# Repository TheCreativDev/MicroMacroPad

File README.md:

# Micro-Macro-Pad!

A small design with 4 Switches and 2 Rotary Encoders for maximum freedom with hotkeys. It's the first hardware I designed, and the first time I worked with both KiCad and Autodesk Fusion, but which was easy and fun to get started thanks to the resources on https://blueprint.hackclub.com/hackpad

## Features
- runs on KMK
- added a little animation that flashes the OLED in a wave pattern on every keystroke

## BOM
- 1 Seeed XIAO RP2040
- 4 MX-Style Switches
- 4 blank DSA keycaps
- 2 EC11 Rotary encoders
- 1 0.91 inch OLED display
- 5 M3x16mm screws
- 5 M3x5mmx4mm heatset inserts
- 6 1N4148 Diodes

## Images of the pad

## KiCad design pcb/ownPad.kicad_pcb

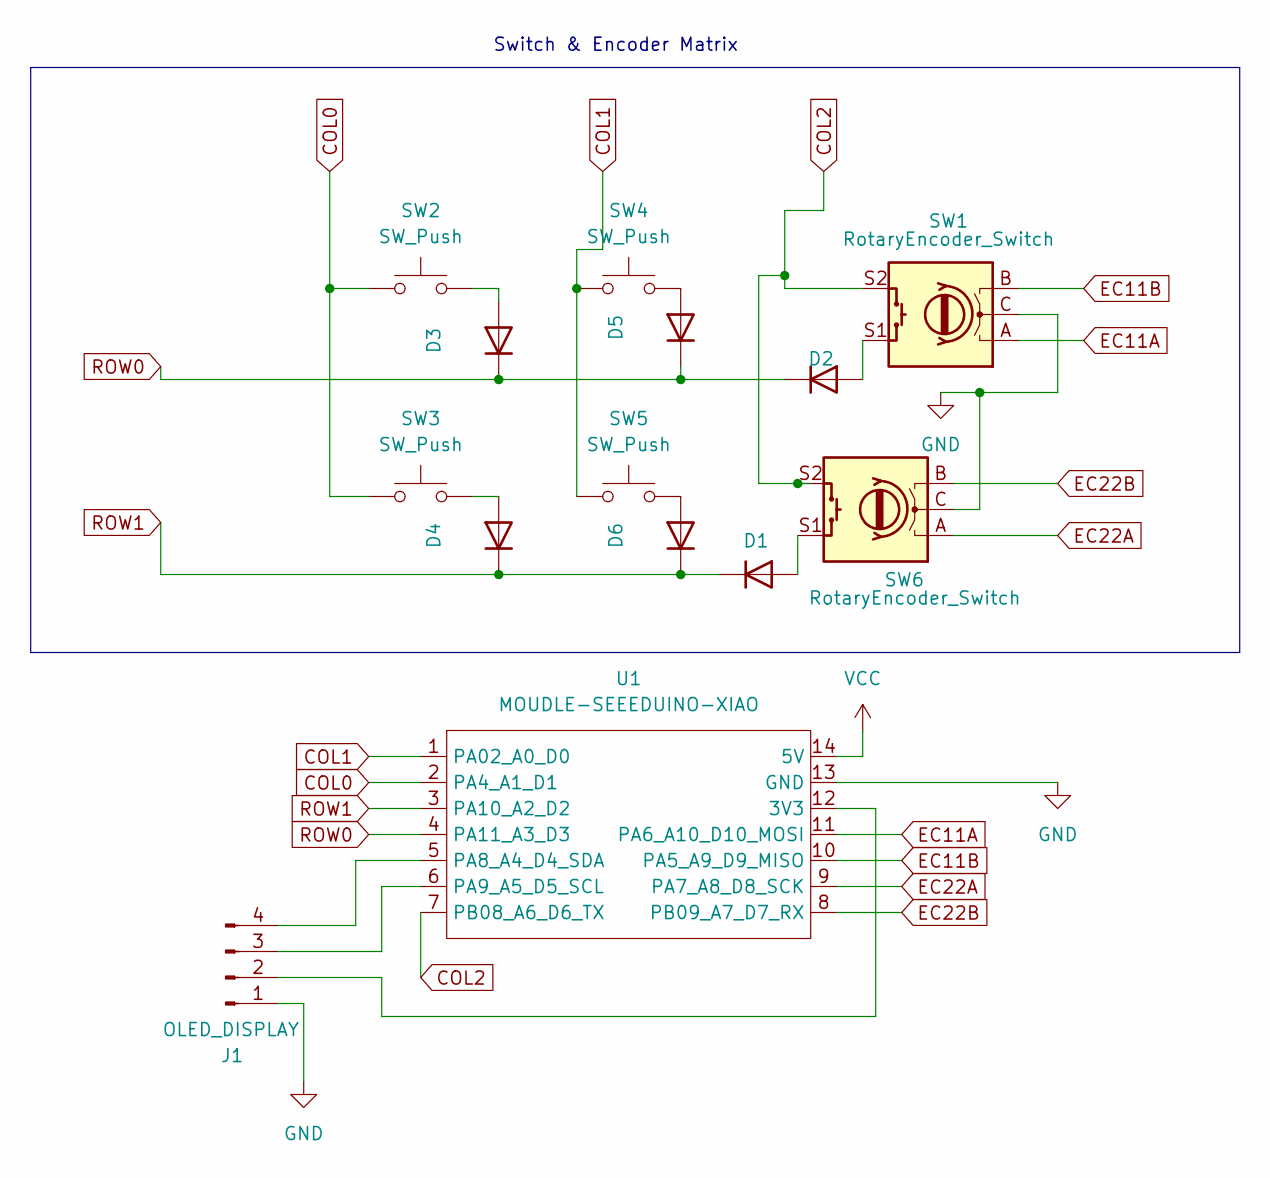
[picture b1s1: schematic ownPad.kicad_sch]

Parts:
D1, D2, D3, D4, D5, D6: D_DO-35_SOD27_P7.62mm_Horizontal
J1: OLED_DISPLAY; SSD1306-0.91-OLED-4pin-128x32
SW1, SW6: RotaryEncoder_Switch; RotaryEncoder_Alps_EC11E-Switch_Vertical_H20mm
SW2, SW3, SW4, SW5: SW_Push; SW_Cherry_MX_1.00u_PCB
U1: MOUDLE-SEEEDUINO-XIAO; XIAO-Generic-Hybrid-14P-2.54-21X17.8MM

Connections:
COL0: SW2.1, SW3.1, U1.2 (PA4_A1_D1)
COL1: SW4.1, SW5.1, U1.1 (PA02_A0_D0)
COL2: SW1.S2, SW6.S2, U1.7 (PB08_A6_D6_TX)
EC11A: SW1.A, U1.11 (PA6_A10_D10_MOSI)
EC11B: SW1.B, U1.10 (PA5_A9_D9_MISO)
EC22A: SW6.A, U1.9 (PA7_A8_D8_SCK)
EC22B: SW6.B, U1.8 (PB09_A7_D7_RX)
GND: J1.1, SW1.C, SW6.C, U1.13 (GND)
unnamed: D1.2 (A), SW6.S1
unnamed: D2.2 (A), SW1.S1
unnamed: D3.2 (A), SW2.2
unnamed: D4.2 (A), SW3.2
unnamed: D5.2 (A), SW4.2
unnamed: D6.2 (A), SW5.2
unnamed: J1.2, U1.12 (3V3)
unnamed: J1.3, U1.6 (PA9_A5_D5_SCL)
unnamed: J1.4, U1.5 (PA8_A4_D4_SDA)
ROW0: D2.1 (K), D3.1 (K), D5.1 (K), U1.4 (PA11_A3_D3)
ROW1: D1.1 (K), D4.1 (K), D6.1 (K), U1.3 (PA10_A2_D2)
VCC: U1.14 (5V)

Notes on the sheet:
Switch & Encoder Matrix

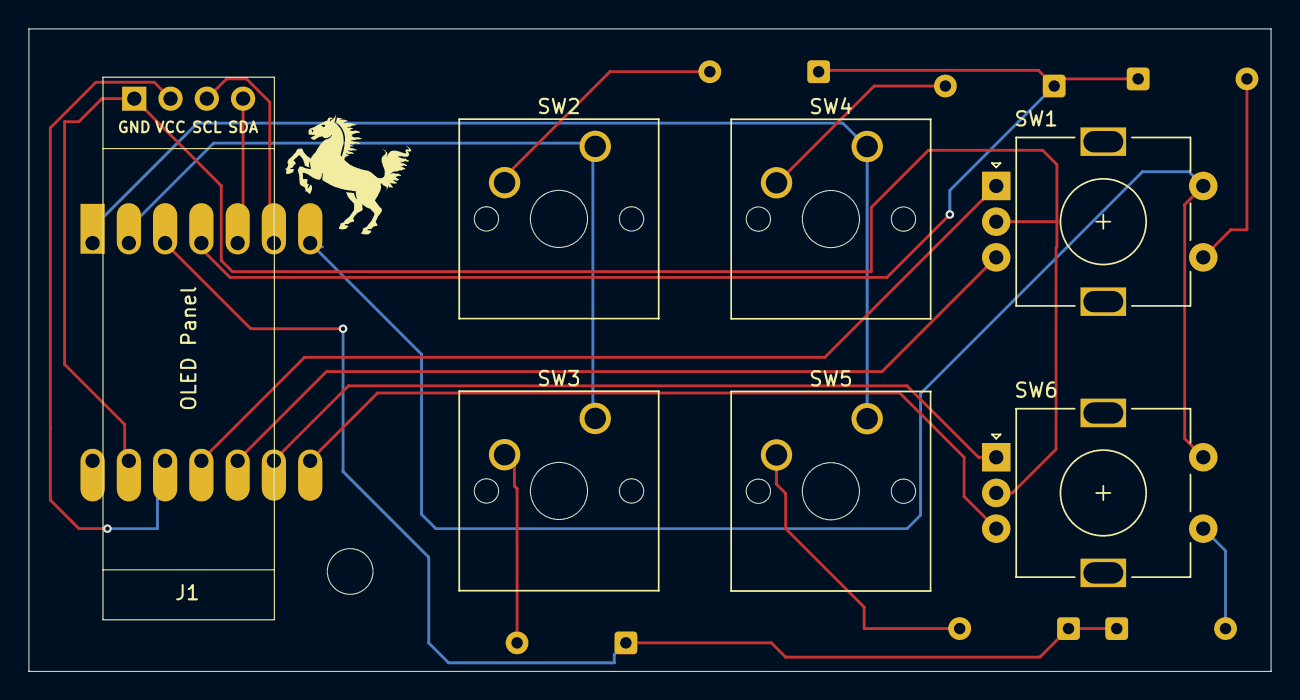
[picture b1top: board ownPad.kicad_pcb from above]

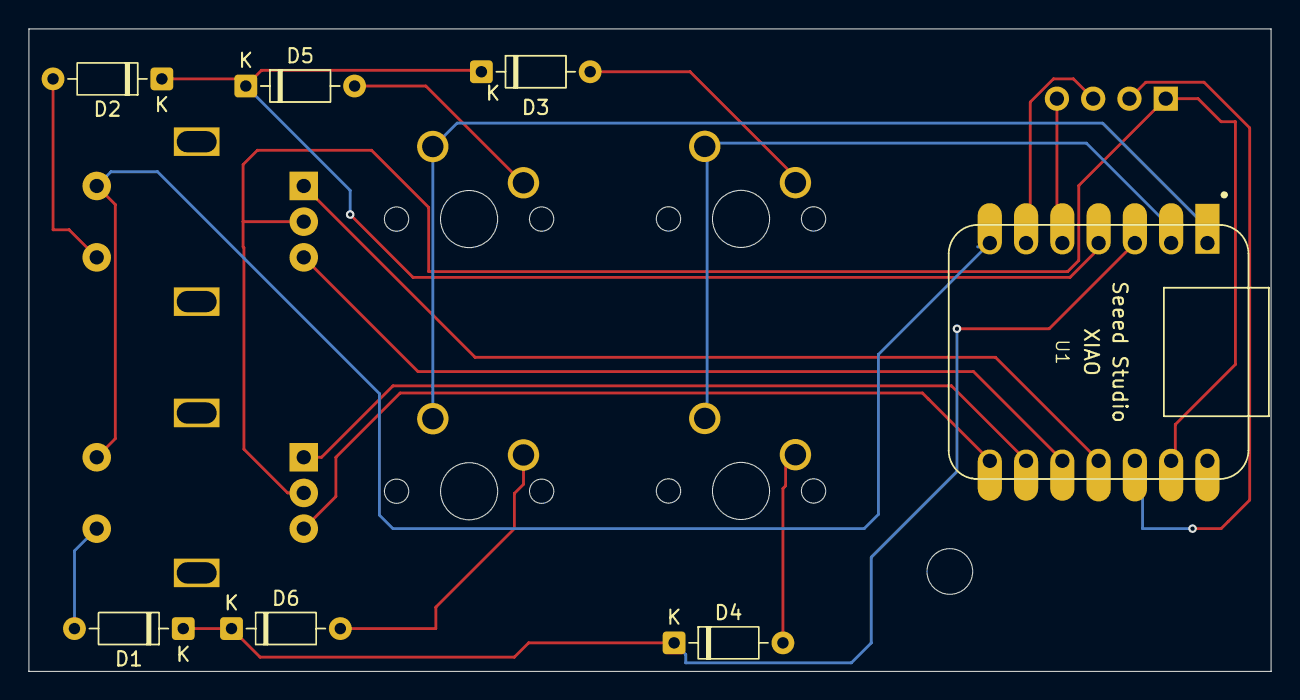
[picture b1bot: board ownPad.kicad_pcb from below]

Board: 2 copper layers, 87.0 x 45.0 mm, 14 parts (7 on the bottom side), 19 nets.

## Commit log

2026-03-15 fixed unconnected traces on pcb
2026-03-17 removed errors in pcb design
2026-03-29 minor gbr fixes
